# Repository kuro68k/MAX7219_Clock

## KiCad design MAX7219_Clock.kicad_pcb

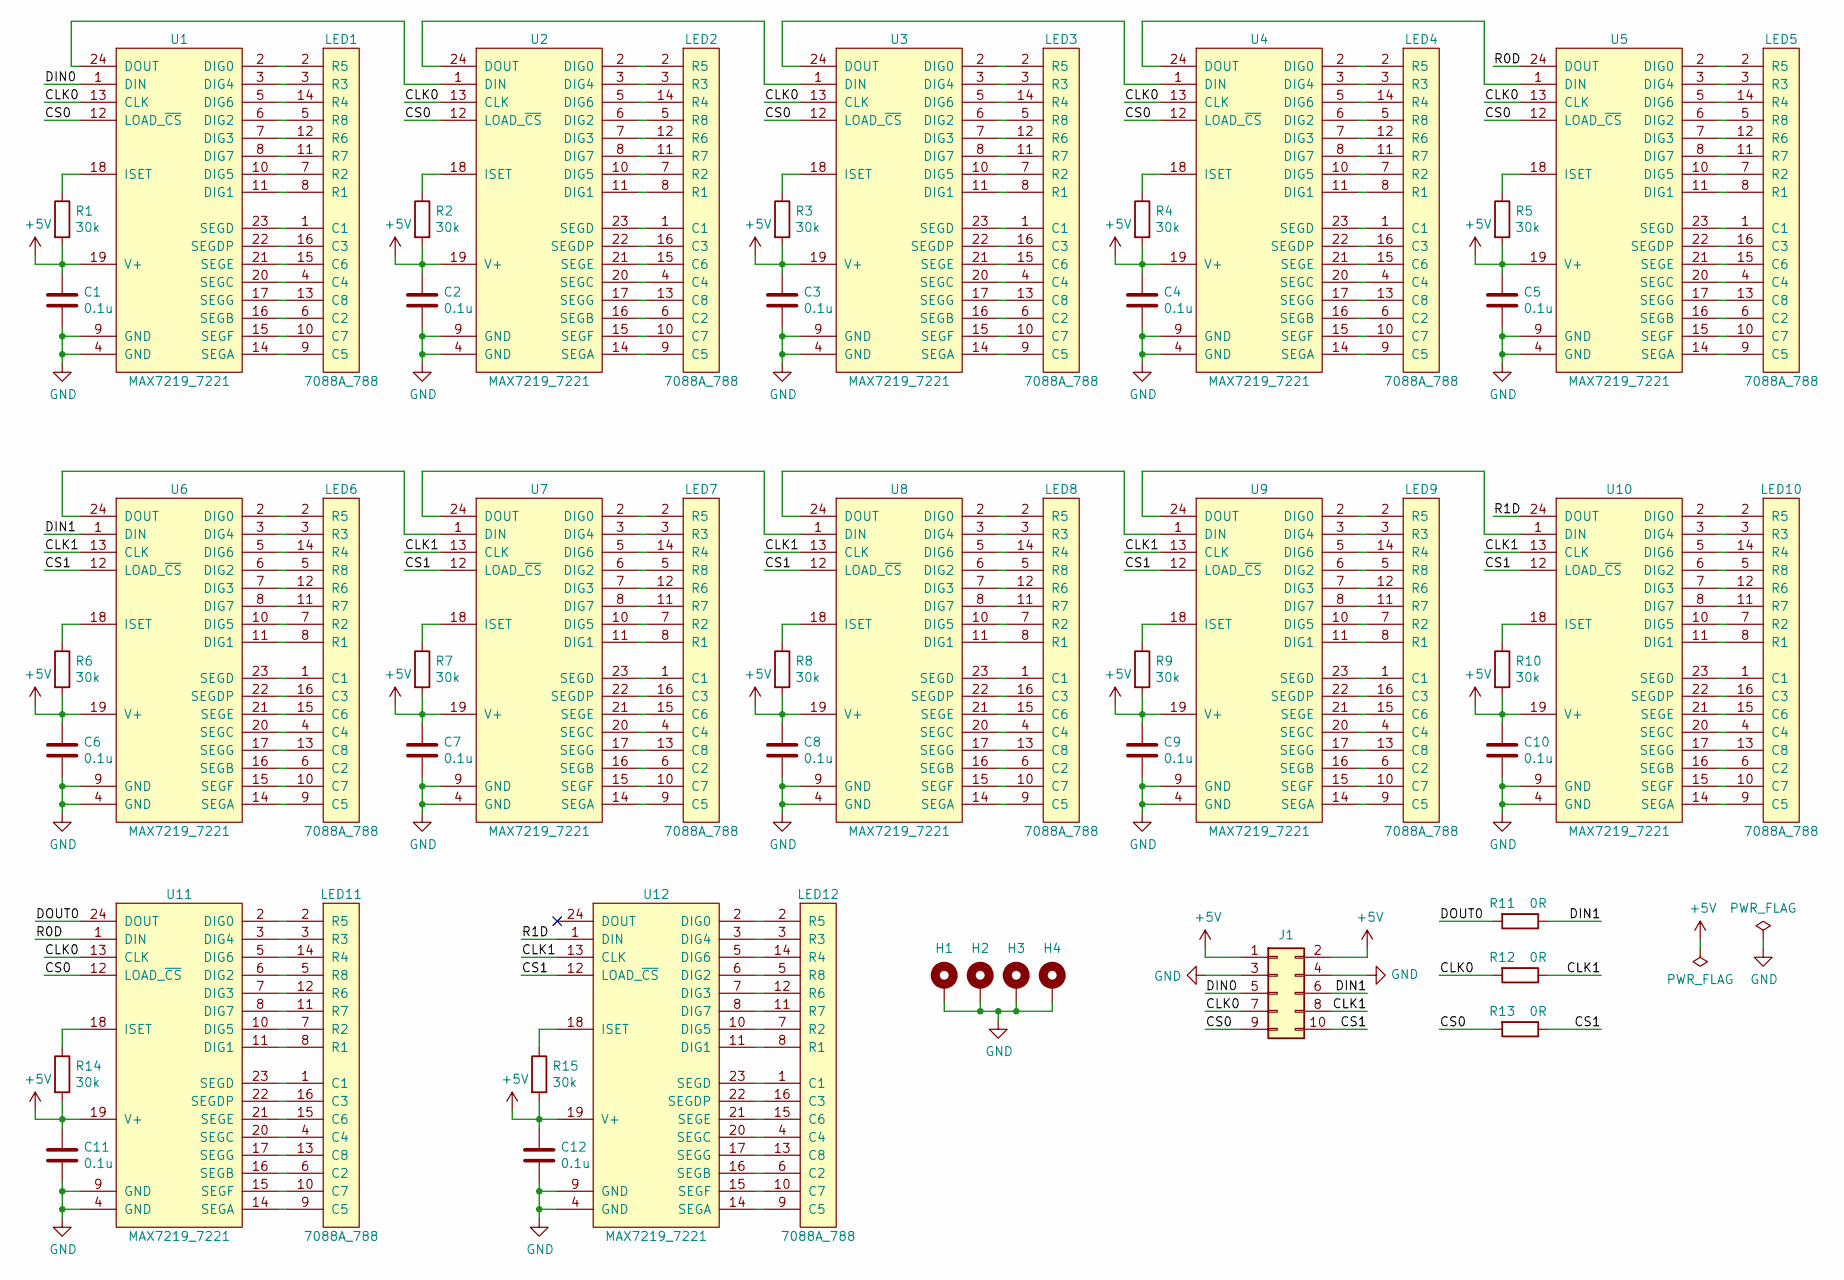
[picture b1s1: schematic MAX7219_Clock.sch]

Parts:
C1, C2, C3, C4, C5, C6, C7, C8, C9, C10, C11, C12: 0.1u; C_0603_1608Metric_Pad1.05x0.95mm_HandSolder
H1, H2, H3, H4: MountingHole_Pad; MountingHole_3.2mm_M3_Pad
J1: Conn_02x05_Odd_Even; PinHeader_2x05_P2.54mm_Vertical
LED1, LED2, LED3, LED4, LED5, LED6, LED7, LED8, LED9, LED10, LED11, LED12: 7088A_788
R1, R2, R3, R4, R5, R6, R7, R8, R9, R10, R14, R15: 30k; R_0603_1608Metric_Pad1.05x0.95mm_HandSolder
R11, R12, R13: 0R; R_0603_1608Metric_Pad1.05x0.95mm_HandSolder
U1, U2, U3, U4, U5, U6, U7, U8, U9, U10, U11, U12: MAX7219_7221; SOIC-24W_7.5x15.4mm_P1.27mm

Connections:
+5V: C1.1, C2.1, C3.1, C4.1, C5.1, C6.1, C7.1, C8.1, C9.1, C10.1, C11.1, C12.1, J1.1, J1.2, R1.2, R2.2, R3.2, R4.2, R5.2, R6.2, R7.2, R8.2, R9.2, R10.2, R14.2, R15.2, U1.19 (V+), U2.19 (V+), U3.19 (V+), U4.19 (V+), U5.19 (V+), U6.19 (V+), U7.19 (V+), U8.19 (V+), U9.19 (V+), U10.19 (V+), U11.19 (V+), U12.19 (V+)
/CLK0: J1.7, R12.2, U1.13 (CLK), U2.13 (CLK), U3.13 (CLK), U4.13 (CLK), U5.13 (CLK), U11.13 (CLK)
/CLK1: J1.8, R12.1, U6.13 (CLK), U7.13 (CLK), U8.13 (CLK), U9.13 (CLK), U10.13 (CLK), U12.13 (CLK)
/CS0: J1.9, R13.2, U1.12 (LOAD_~CS), U2.12 (LOAD_~CS), U3.12 (LOAD_~CS), U4.12 (LOAD_~CS), U5.12 (LOAD_~CS), U11.12 (LOAD_~CS)
/CS1: J1.10, R13.1, U6.12 (LOAD_~CS), U7.12 (LOAD_~CS), U8.12 (LOAD_~CS), U9.12 (LOAD_~CS), U10.12 (LOAD_~CS), U12.12 (LOAD_~CS)
/DIN0: J1.5, U1.1 (DIN)
/DIN1: J1.6, R11.1, U6.1 (DIN)
/DOUT0: R11.2, U11.24 (DOUT)
/R0D: U5.24 (DOUT), U11.1 (DIN)
/R1D: U10.24 (DOUT), U12.1 (DIN)
GND: C1.2, C2.2, C3.2, C4.2, C5.2, C6.2, C7.2, C8.2, C9.2, C10.2, C11.2, C12.2, H1.1, H2.1, H3.1, H4.1, J1.3, J1.4, U1.4 (GND), U1.9 (GND), U2.4 (GND), U2.9 (GND), U3.4 (GND), U3.9 (GND), U4.4 (GND), U4.9 (GND), U5.4 (GND), U5.9 (GND), U6.4 (GND), U6.9 (GND), U7.4 (GND), U7.9 (GND), U8.4 (GND), U8.9 (GND), U9.4 (GND), U9.9 (GND), U10.4 (GND), U10.9 (GND), U11.4 (GND), U11.9 (GND), U12.4 (GND), U12.9 (GND)
unnamed: LED1.1 (C1), U1.23 (SEGD)
unnamed: LED1.2 (R5), U1.2 (DIG0)
unnamed: LED1.3 (R3), U1.3 (DIG4)
unnamed: LED1.4 (C4), U1.20 (SEGC)
unnamed: LED1.5 (R8), U1.6 (DIG2)
unnamed: LED1.6 (C2), U1.16 (SEGB)
unnamed: LED1.7 (R2), U1.10 (DIG5)
unnamed: LED1.8 (R1), U1.11 (DIG1)
unnamed: LED1.9 (C5), U1.14 (SEGA)
unnamed: LED1.10 (C7), U1.15 (SEGF)
unnamed: LED1.11 (R7), U1.8 (DIG7)
unnamed: LED1.12 (R6), U1.7 (DIG3)
unnamed: LED1.13 (C8), U1.17 (SEGG)
unnamed: LED1.14 (R4), U1.5 (DIG6)
unnamed: LED1.15 (C6), U1.21 (SEGE)
unnamed: LED1.16 (C3), U1.22 (SEGDP)
unnamed: LED2.1 (C1), U2.23 (SEGD)
unnamed: LED2.2 (R5), U2.2 (DIG0)
unnamed: LED2.3 (R3), U2.3 (DIG4)
unnamed: LED2.4 (C4), U2.20 (SEGC)
unnamed: LED2.5 (R8), U2.6 (DIG2)
unnamed: LED2.6 (C2), U2.16 (SEGB)
unnamed: LED2.7 (R2), U2.10 (DIG5)
unnamed: LED2.8 (R1), U2.11 (DIG1)
unnamed: LED2.9 (C5), U2.14 (SEGA)
unnamed: LED2.10 (C7), U2.15 (SEGF)
unnamed: LED2.11 (R7), U2.8 (DIG7)
unnamed: LED2.12 (R6), U2.7 (DIG3)
unnamed: LED2.13 (C8), U2.17 (SEGG)
unnamed: LED2.14 (R4), U2.5 (DIG6)
unnamed: LED2.15 (C6), U2.21 (SEGE)
unnamed: LED2.16 (C3), U2.22 (SEGDP)
unnamed: LED3.1 (C1), U3.23 (SEGD)
unnamed: LED3.2 (R5), U3.2 (DIG0)
unnamed: LED3.3 (R3), U3.3 (DIG4)
unnamed: LED3.4 (C4), U3.20 (SEGC)
unnamed: LED3.5 (R8), U3.6 (DIG2)
unnamed: LED3.6 (C2), U3.16 (SEGB)
unnamed: LED3.7 (R2), U3.10 (DIG5)
unnamed: LED3.8 (R1), U3.11 (DIG1)
unnamed: LED3.9 (C5), U3.14 (SEGA)
unnamed: LED3.10 (C7), U3.15 (SEGF)
unnamed: LED3.11 (R7), U3.8 (DIG7)
unnamed: LED3.12 (R6), U3.7 (DIG3)
unnamed: LED3.13 (C8), U3.17 (SEGG)
unnamed: LED3.14 (R4), U3.5 (DIG6)
unnamed: LED3.15 (C6), U3.21 (SEGE)
unnamed: LED3.16 (C3), U3.22 (SEGDP)
unnamed: LED4.1 (C1), U4.23 (SEGD)
unnamed: LED4.2 (R5), U4.2 (DIG0)
unnamed: LED4.3 (R3), U4.3 (DIG4)
unnamed: LED4.4 (C4), U4.20 (SEGC)
unnamed: LED4.5 (R8), U4.6 (DIG2)
unnamed: LED4.6 (C2), U4.16 (SEGB)
unnamed: LED4.7 (R2), U4.10 (DIG5)
unnamed: LED4.8 (R1), U4.11 (DIG1)
unnamed: LED4.9 (C5), U4.14 (SEGA)
unnamed: LED4.10 (C7), U4.15 (SEGF)
unnamed: LED4.11 (R7), U4.8 (DIG7)
unnamed: LED4.12 (R6), U4.7 (DIG3)
unnamed: LED4.13 (C8), U4.17 (SEGG)
unnamed: LED4.14 (R4), U4.5 (DIG6)
unnamed: LED4.15 (C6), U4.21 (SEGE)
unnamed: LED4.16 (C3), U4.22 (SEGDP)
unnamed: LED5.1 (C1), U5.23 (SEGD)
unnamed: LED5.2 (R5), U5.2 (DIG0)
unnamed: LED5.3 (R3), U5.3 (DIG4)
unnamed: LED5.4 (C4), U5.20 (SEGC)
unnamed: LED5.5 (R8), U5.6 (DIG2)
unnamed: LED5.6 (C2), U5.16 (SEGB)
unnamed: LED5.7 (R2), U5.10 (DIG5)
unnamed: LED5.8 (R1), U5.11 (DIG1)
unnamed: LED5.9 (C5), U5.14 (SEGA)
unnamed: LED5.10 (C7), U5.15 (SEGF)
unnamed: LED5.11 (R7), U5.8 (DIG7)
unnamed: LED5.12 (R6), U5.7 (DIG3)
unnamed: LED5.13 (C8), U5.17 (SEGG)
unnamed: LED5.14 (R4), U5.5 (DIG6)
unnamed: LED5.15 (C6), U5.21 (SEGE)
unnamed: LED5.16 (C3), U5.22 (SEGDP)
unnamed: LED6.1 (C1), U6.23 (SEGD)
unnamed: LED6.2 (R5), U6.2 (DIG0)
unnamed: LED6.3 (R3), U6.3 (DIG4)
unnamed: LED6.4 (C4), U6.20 (SEGC)
unnamed: LED6.5 (R8), U6.6 (DIG2)
unnamed: LED6.6 (C2), U6.16 (SEGB)
unnamed: LED6.7 (R2), U6.10 (DIG5)
unnamed: LED6.8 (R1), U6.11 (DIG1)
unnamed: LED6.9 (C5), U6.14 (SEGA)
unnamed: LED6.10 (C7), U6.15 (SEGF)
unnamed: LED6.11 (R7), U6.8 (DIG7)
unnamed: LED6.12 (R6), U6.7 (DIG3)
unnamed: LED6.13 (C8), U6.17 (SEGG)
unnamed: LED6.14 (R4), U6.5 (DIG6)
unnamed: LED6.15 (C6), U6.21 (SEGE)
unnamed: LED6.16 (C3), U6.22 (SEGDP)
unnamed: LED7.1 (C1), U7.23 (SEGD)
unnamed: LED7.2 (R5), U7.2 (DIG0)
unnamed: LED7.3 (R3), U7.3 (DIG4)
unnamed: LED7.4 (C4), U7.20 (SEGC)
unnamed: LED7.5 (R8), U7.6 (DIG2)
unnamed: LED7.6 (C2), U7.16 (SEGB)
unnamed: LED7.7 (R2), U7.10 (DIG5)
unnamed: LED7.8 (R1), U7.11 (DIG1)
unnamed: LED7.9 (C5), U7.14 (SEGA)
unnamed: LED7.10 (C7), U7.15 (SEGF)
unnamed: LED7.11 (R7), U7.8 (DIG7)
unnamed: LED7.12 (R6), U7.7 (DIG3)
unnamed: LED7.13 (C8), U7.17 (SEGG)
unnamed: LED7.14 (R4), U7.5 (DIG6)
unnamed: LED7.15 (C6), U7.21 (SEGE)
unnamed: LED7.16 (C3), U7.22 (SEGDP)
unnamed: LED8.1 (C1), U8.23 (SEGD)
unnamed: LED8.2 (R5), U8.2 (DIG0)
unnamed: LED8.3 (R3), U8.3 (DIG4)
unnamed: LED8.4 (C4), U8.20 (SEGC)
unnamed: LED8.5 (R8), U8.6 (DIG2)
unnamed: LED8.6 (C2), U8.16 (SEGB)
unnamed: LED8.7 (R2), U8.10 (DIG5)
unnamed: LED8.8 (R1), U8.11 (DIG1)
unnamed: LED8.9 (C5), U8.14 (SEGA)
unnamed: LED8.10 (C7), U8.15 (SEGF)
unnamed: LED8.11 (R7), U8.8 (DIG7)
unnamed: LED8.12 (R6), U8.7 (DIG3)
unnamed: LED8.13 (C8), U8.17 (SEGG)
unnamed: LED8.14 (R4), U8.5 (DIG6)
unnamed: LED8.15 (C6), U8.21 (SEGE)
unnamed: LED8.16 (C3), U8.22 (SEGDP)
unnamed: LED9.1 (C1), U9.23 (SEGD)
unnamed: LED9.2 (R5), U9.2 (DIG0)
unnamed: LED9.3 (R3), U9.3 (DIG4)
unnamed: LED9.4 (C4), U9.20 (SEGC)
unnamed: LED9.5 (R8), U9.6 (DIG2)
unnamed: LED9.6 (C2), U9.16 (SEGB)
unnamed: LED9.7 (R2), U9.10 (DIG5)
unnamed: LED9.8 (R1), U9.11 (DIG1)
unnamed: LED9.9 (C5), U9.14 (SEGA)
unnamed: LED9.10 (C7), U9.15 (SEGF)
unnamed: LED9.11 (R7), U9.8 (DIG7)
unnamed: LED9.12 (R6), U9.7 (DIG3)
unnamed: LED9.13 (C8), U9.17 (SEGG)
unnamed: LED9.14 (R4), U9.5 (DIG6)
unnamed: LED9.15 (C6), U9.21 (SEGE)
unnamed: LED9.16 (C3), U9.22 (SEGDP)
unnamed: LED10.1 (C1), U10.23 (SEGD)
unnamed: LED10.2 (R5), U10.2 (DIG0)
unnamed: LED10.3 (R3), U10.3 (DIG4)
unnamed: LED10.4 (C4), U10.20 (SEGC)
unnamed: LED10.5 (R8), U10.6 (DIG2)
unnamed: LED10.6 (C2), U10.16 (SEGB)
unnamed: LED10.7 (R2), U10.10 (DIG5)
unnamed: LED10.8 (R1), U10.11 (DIG1)
unnamed: LED10.9 (C5), U10.14 (SEGA)
unnamed: LED10.10 (C7), U10.15 (SEGF)
unnamed: LED10.11 (R7), U10.8 (DIG7)
unnamed: LED10.12 (R6), U10.7 (DIG3)
unnamed: LED10.13 (C8), U10.17 (SEGG)
unnamed: LED10.14 (R4), U10.5 (DIG6)
unnamed: LED10.15 (C6), U10.21 (SEGE)
unnamed: LED10.16 (C3), U10.22 (SEGDP)
unnamed: LED11.1 (C1), U11.23 (SEGD)
unnamed: LED11.2 (R5), U11.2 (DIG0)
unnamed: LED11.3 (R3), U11.3 (DIG4)
unnamed: LED11.4 (C4), U11.20 (SEGC)
unnamed: LED11.5 (R8), U11.6 (DIG2)
unnamed: LED11.6 (C2), U11.16 (SEGB)
unnamed: LED11.7 (R2), U11.10 (DIG5)
unnamed: LED11.8 (R1), U11.11 (DIG1)
unnamed: LED11.9 (C5), U11.14 (SEGA)
unnamed: LED11.10 (C7), U11.15 (SEGF)
unnamed: LED11.11 (R7), U11.8 (DIG7)
unnamed: LED11.12 (R6), U11.7 (DIG3)
unnamed: LED11.13 (C8), U11.17 (SEGG)
unnamed: LED11.14 (R4), U11.5 (DIG6)
unnamed: LED11.15 (C6), U11.21 (SEGE)
unnamed: LED11.16 (C3), U11.22 (SEGDP)
unnamed: LED12.1 (C1), U12.23 (SEGD)
unnamed: LED12.2 (R5), U12.2 (DIG0)
unnamed: LED12.3 (R3), U12.3 (DIG4)
unnamed: LED12.4 (C4), U12.20 (SEGC)
unnamed: LED12.5 (R8), U12.6 (DIG2)
unnamed: LED12.6 (C2), U12.16 (SEGB)
unnamed: LED12.7 (R2), U12.10 (DIG5)
unnamed: LED12.8 (R1), U12.11 (DIG1)
unnamed: LED12.9 (C5), U12.14 (SEGA)
unnamed: LED12.10 (C7), U12.15 (SEGF)
unnamed: LED12.11 (R7), U12.8 (DIG7)
unnamed: LED12.12 (R6), U12.7 (DIG3)
unnamed: LED12.13 (C8), U12.17 (SEGG)
unnamed: LED12.14 (R4), U12.5 (DIG6)
unnamed: LED12.15 (C6), U12.21 (SEGE)
unnamed: LED12.16 (C3), U12.22 (SEGDP)
unnamed: R1.1, U1.18 (ISET)
unnamed: R2.1, U2.18 (ISET)
unnamed: R3.1, U3.18 (ISET)
unnamed: R4.1, U4.18 (ISET)
unnamed: R5.1, U5.18 (ISET)
unnamed: R6.1, U6.18 (ISET)
unnamed: R7.1, U7.18 (ISET)
unnamed: R8.1, U8.18 (ISET)
unnamed: R9.1, U9.18 (ISET)
unnamed: R10.1, U10.18 (ISET)
unnamed: R14.1, U11.18 (ISET)
unnamed: R15.1, U12.18 (ISET)
unnamed: U1.24 (DOUT), U2.1 (DIN)
unnamed: U2.24 (DOUT), U3.1 (DIN)
unnamed: U3.24 (DOUT), U4.1 (DIN)
unnamed: U4.24 (DOUT), U5.1 (DIN)
unnamed: U6.24 (DOUT), U7.1 (DIN)
unnamed: U7.24 (DOUT), U8.1 (DIN)
unnamed: U8.24 (DOUT), U9.1 (DIN)
unnamed: U9.24 (DOUT), U10.1 (DIN)

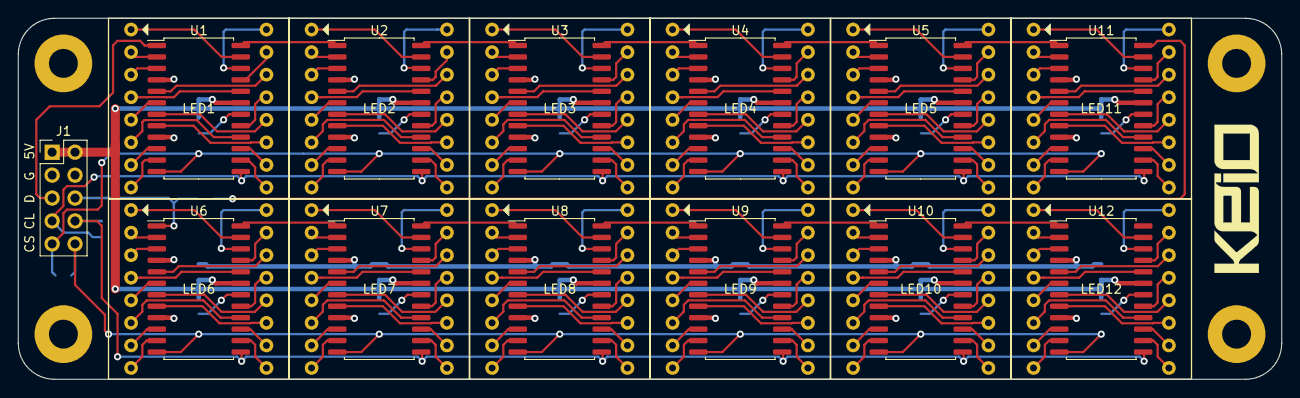
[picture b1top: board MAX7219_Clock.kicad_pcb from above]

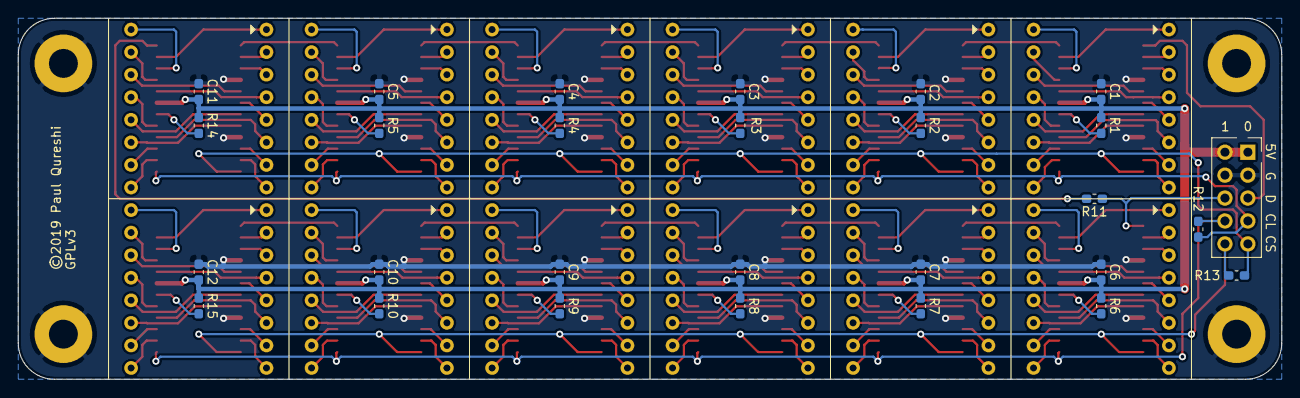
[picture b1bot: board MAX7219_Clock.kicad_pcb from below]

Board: 2 copper layers, 140.0 x 40.0 mm, 56 parts (27 on the bottom side), 223 nets.

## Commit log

2019-11-29 Gerbers for Seeed
2019-11-29 PDF schematic
2019-11-29 Plot settings
2019-11-29 Rounded corners

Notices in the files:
MAX7219_Clock.kicad_pcb:
©2019 Paul Qureshi
GPLv3
